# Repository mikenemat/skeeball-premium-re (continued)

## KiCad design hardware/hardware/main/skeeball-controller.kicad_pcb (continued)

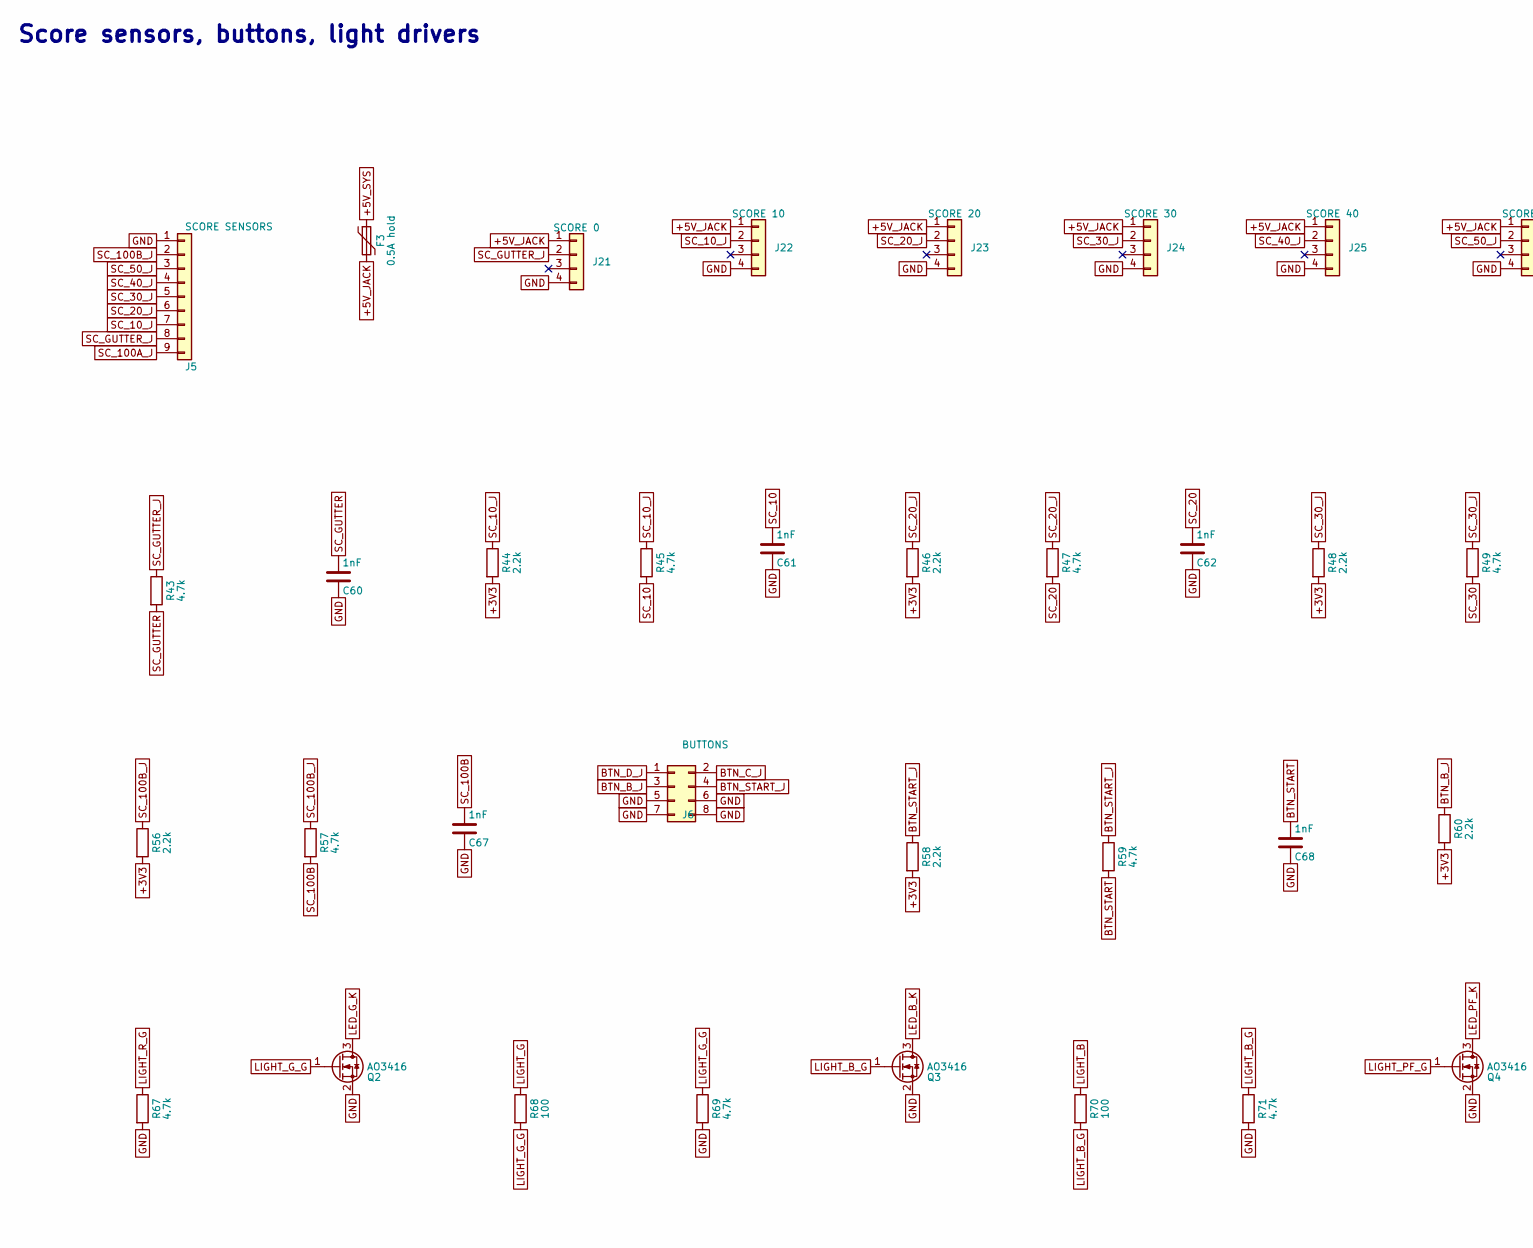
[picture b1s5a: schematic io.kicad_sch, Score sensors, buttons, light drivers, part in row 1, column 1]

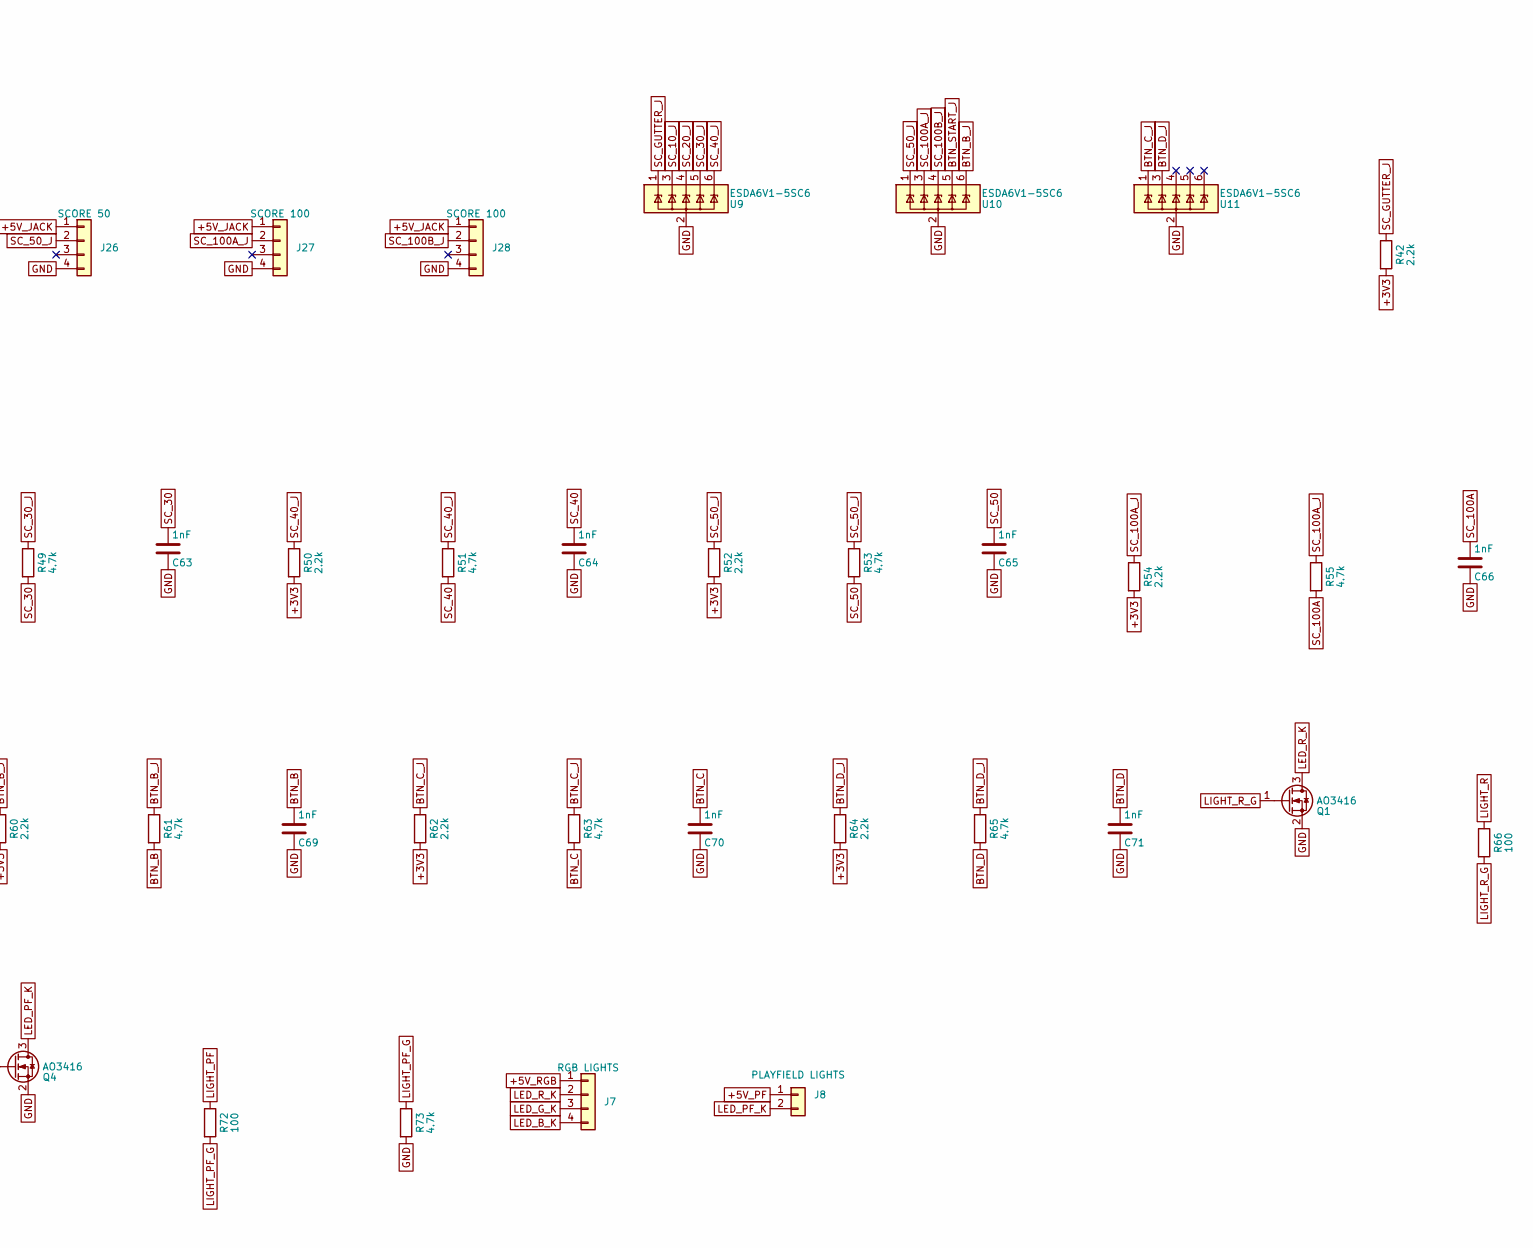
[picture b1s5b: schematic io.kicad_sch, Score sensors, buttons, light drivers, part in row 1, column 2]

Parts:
C60, C61, C62, C63, C64, C65, C66, C67, C68, C69, C70, C71: 1nF; C_0603_1608Metric; MPN CL10B102KB8NNNC
F3: 0.5A hold; Fuse_1206_3216Metric; MPN MF-NSMF050-2; LCSC C75464
J5: SCORE SENSORS; PinHeader_1x09_P2.54mm_Vertical; MPN HC-PZ254-11.5L-1x9PZ; LCSC C27985193
J6: BUTTONS; Molex_Mini-Fit_Jr_5566-08A_2x04_P4.20mm_Vertical; MPN 39281083; LCSC C293503
J7: RGB LIGHTS; Molex_Mini-Fit_Jr_39-30-1049_1x04_P4.20mm_Vertical; MPN 39301049; LCSC C587488
J8: PLAYFIELD LIGHTS; Molex_KK-396_A-41791-0002_1x02_P3.96mm_Vertical; MPN 26604020; LCSC C505042
J21: SCORE 0; RJ11_6P4C_TopEntry_StockPads; MPN 955032441; LCSC C588833
J22: SCORE 10; RJ11_6P4C_TopEntry_StockPads; MPN 955032441; LCSC C588833
J23: SCORE 20; RJ11_6P4C_TopEntry_StockPads; MPN 955032441; LCSC C588833
J24: SCORE 30; RJ11_6P4C_TopEntry_StockPads; MPN 955032441; LCSC C588833
J25: SCORE 40; RJ11_6P4C_TopEntry_StockPads; MPN 955032441; LCSC C588833
J26: SCORE 50; RJ11_6P4C_TopEntry_StockPads; MPN 955032441; LCSC C588833
J27, J28: SCORE 100; RJ11_6P4C_TopEntry_StockPads; MPN 955032441; LCSC C588833
Q1, Q2, Q3, Q4: AO3416; SOT-23; MPN AO3416; LCSC C43307
R42, R44, R46, R48, R50, R52, R54, R56, R58, R60, R62, R64: 2.2k; R_0603_1608Metric; tolerance 1%; MPN 0603WAF2201T5E
R43, R45, R47, R49, R51, R53, R55, R57, R59, R61, R63, R65, R67, R69, R71, R73: 4.7k; R_0603_1608Metric; tolerance 1%; MPN 0603WAF4701T5E
R66, R68, R70, R72: 100; R_0603_1608Metric; tolerance 1%; MPN 0603WAF1000T5E
U9, U10, U11: ESDA6V1-5SC6; SOT-23-6; MPN ESDA6V1-5SC6; LCSC C6650

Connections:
+3V3: R42.2, R44.2, R46.2, R48.2, R50.2, R52.2, R54.2, R56.2, R58.2, R60.2, R62.2, R64.2; also elsewhere on the board
+5V_JACK: F3.2, J21.1, J22.1, J23.1, J24.1, J25.1, J26.1, J27.1, J28.1
+5V_PF: J8.1; also elsewhere on the board
+5V_RGB: J7.1; also elsewhere on the board
+5V_SYS: F3.1; also elsewhere on the board
BTN_B: C69.1, R61.2; also elsewhere on the board
BTN_B_J: J6.3, R60.1, R61.1, U10.6 (IO5)
BTN_C: C70.1, R63.2; also elsewhere on the board
BTN_C_J: J6.2, R62.1, R63.1, U11.1 (IO1)
BTN_D: C71.1, R65.2; also elsewhere on the board
BTN_D_J: J6.1, R64.1, R65.1, U11.3 (IO2)
BTN_START: C68.1, R59.2; also elsewhere on the board
BTN_START_J: J6.4, R58.1, R59.1, U10.5 (IO4)
GND: C60.2, C61.2, C62.2, C63.2, C64.2, C65.2, C66.2, C67.2, C68.2, C69.2, C70.2, C71.2, J5.1, J6.5, J6.6, J6.7, J6.8, J21.4, J22.4, J23.4, J24.4, J25.4, J26.4, J27.4, J28.4, Q1.2 (S), Q2.2 (S), Q3.2 (S), Q4.2 (S), R67.2, R69.2, R71.2, R73.2, U9.2 (GND), U10.2 (GND), U11.2 (GND); also elsewhere on the board
LED_B_K: J7.4, Q3.3 (D)
LED_G_K: J7.3, Q2.3 (D)
LED_PF_K: J8.2, Q4.3 (D)
LED_R_K: J7.2, Q1.3 (D)
LIGHT_B: R70.1; also elsewhere on the board
LIGHT_B_G: Q3.1 (G), R70.2, R71.1
LIGHT_G: R68.1; also elsewhere on the board
LIGHT_G_G: Q2.1 (G), R68.2, R69.1
LIGHT_PF: R72.1; also elsewhere on the board
LIGHT_PF_G: Q4.1 (G), R72.2, R73.1
LIGHT_R: R66.1; also elsewhere on the board
LIGHT_R_G: Q1.1 (G), R66.2, R67.1
SC_10: C61.1, R45.2; also elsewhere on the board
SC_10_J: J5.7, J22.2, R44.1, R45.1, U9.3 (IO2)
SC_20: C62.1, R47.2; also elsewhere on the board
SC_20_J: J5.6, J23.2, R46.1, R47.1, U9.4 (IO3)
SC_30: C63.1, R49.2; also elsewhere on the board
SC_30_J: J5.5, J24.2, R48.1, R49.1, U9.5 (IO4)
SC_40: C64.1, R51.2; also elsewhere on the board
SC_40_J: J5.4, J25.2, R50.1, R51.1, U9.6 (IO5)
SC_50: C65.1, R53.2; also elsewhere on the board
SC_50_J: J5.3, J26.2, R52.1, R53.1, U10.1 (IO1)
SC_100A: C66.1, R55.2; also elsewhere on the board
SC_100A_J: J5.9, J27.2, R54.1, R55.1, U10.3 (IO2)
SC_100B: C67.1, R57.2; also elsewhere on the board
SC_100B_J: J5.2, J28.2, R56.1, R57.1, U10.4 (IO3)
SC_GUTTER: C60.1, R43.2; also elsewhere on the board
SC_GUTTER_J: J5.8, J21.2, R42.1, R43.1, U9.1 (IO1)

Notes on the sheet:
Score sensors, buttons, light drivers

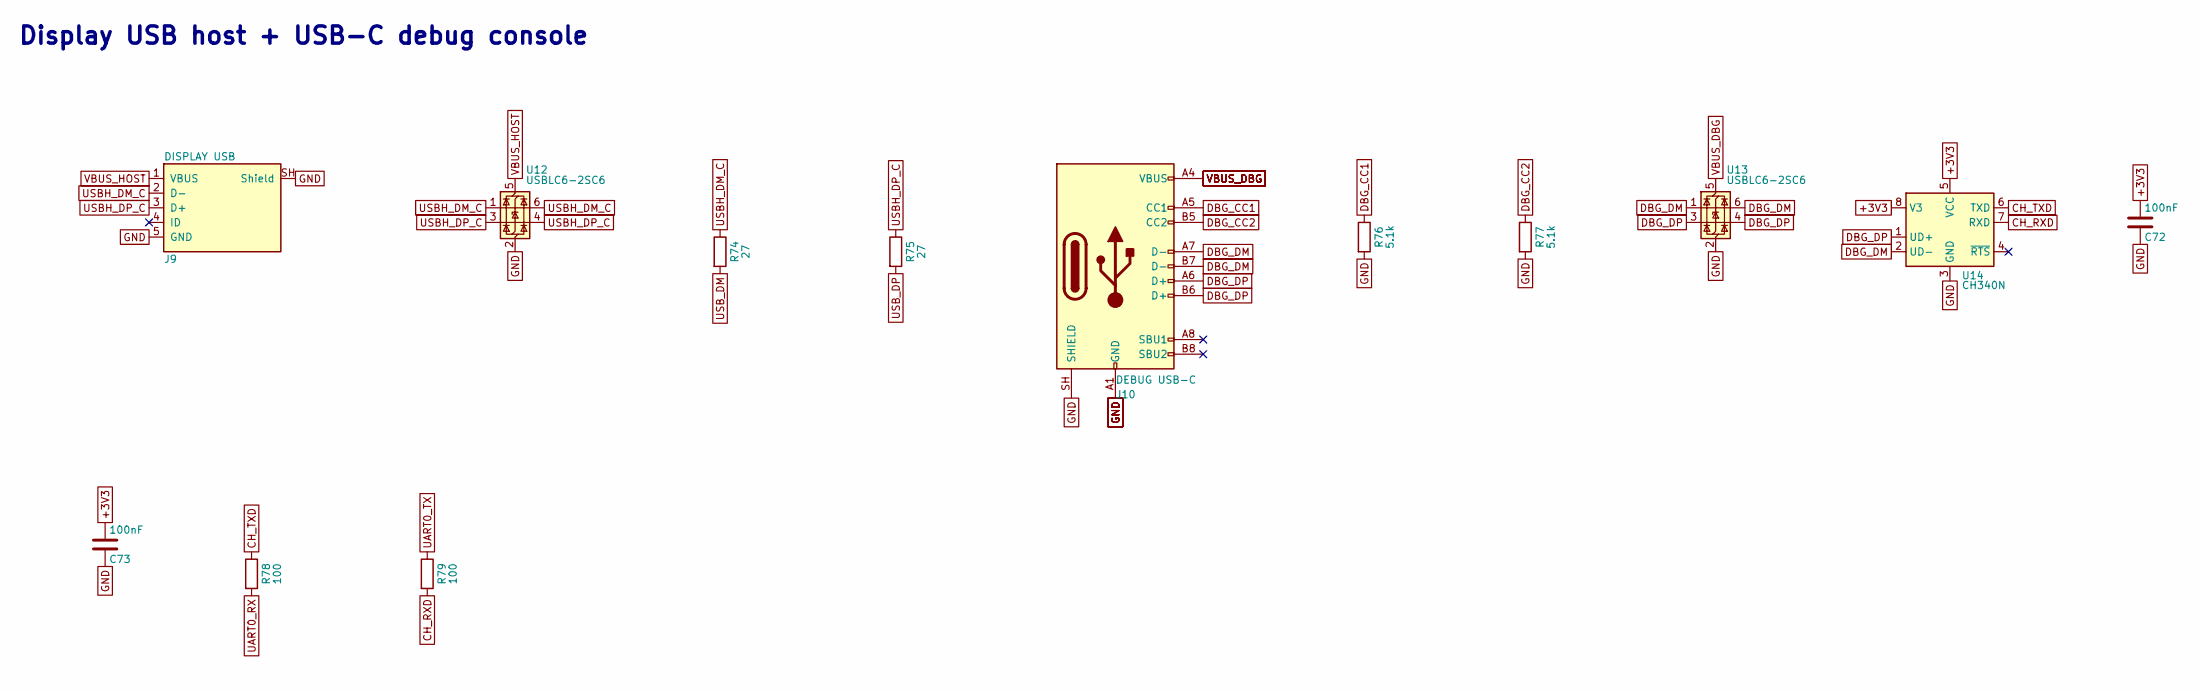
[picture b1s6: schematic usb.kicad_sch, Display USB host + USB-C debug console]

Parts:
C72, C73: 100nF; C_0603_1608Metric; MPN CC0603KRX7R9BB104
J9: DISPLAY USB; USB_Micro-B_Amphenol_10118194-0001LF_Horizontal; MPN 10118194-0001LF; LCSC C132563
J10: DEBUG USB-C; USB_C_Receptacle_HRO_TYPE-C-31-D-15_Vertical; MPN TYPE-C-31-D-15; LCSC C22464480
R74, R75: 27; R_0603_1608Metric; tolerance 1%; MPN 0603WAF270JT5E
R76, R77: 5.1k; R_0603_1608Metric; tolerance 1%; MPN 0603WAF5101T5E
R78, R79: 100; R_0603_1608Metric; tolerance 1%; MPN 0603WAF1000T5E
U12, U13: USBLC6-2SC6; SOT-23-6; MPN USBLC6-2SC6; LCSC C7519
U14: CH340N; SOIC-8_3.9x4.9mm_P1.27mm; MPN CH340N; LCSC C2977777

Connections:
+3V3: C72.1, C73.1, U14.5 (VCC), U14.8 (V3); also elsewhere on the board
CH_RXD: R79.2, U14.7 (RXD)
CH_TXD: R78.1, U14.6 (TXD)
DBG_CC1: J10.A5 (CC1), R76.1
DBG_CC2: J10.B5 (CC2), R77.1
DBG_DM: J10.A7 (D-), J10.B7 (D-), U13.1 (I/O1), U13.6 (I/O1), U14.2 (UD-)
DBG_DP: J10.A6 (D+), J10.B6 (D+), U13.3 (I/O2), U13.4 (I/O2), U14.1 (UD+)
GND: C72.2, C73.2, J9.5 (GND), J9.SH (Shield), J10.A1 (GND), J10.A12 (GND), J10.B1 (GND), J10.B12 (GND), J10.SH (SHIELD), R76.2, R77.2, U12.2 (GND), U13.2 (GND), U14.3 (GND); also elsewhere on the board
UART0_RX: R78.2; also elsewhere on the board
UART0_TX: R79.1; also elsewhere on the board
USBH_DM_C: J9.2 (D-), R74.1, U12.1 (I/O1), U12.6 (I/O1)
USBH_DP_C: J9.3 (D+), R75.1, U12.3 (I/O2), U12.4 (I/O2)
USB_DM: R74.2; also elsewhere on the board
USB_DP: R75.2; also elsewhere on the board
VBUS_DBG: J10.A4 (VBUS), J10.A9 (VBUS), J10.B4 (VBUS), J10.B9 (VBUS), U13.5 (VBUS)
VBUS_HOST: J9.1 (VBUS), U12.5 (VBUS); also elsewhere on the board

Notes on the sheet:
Display USB host + USB-C debug console

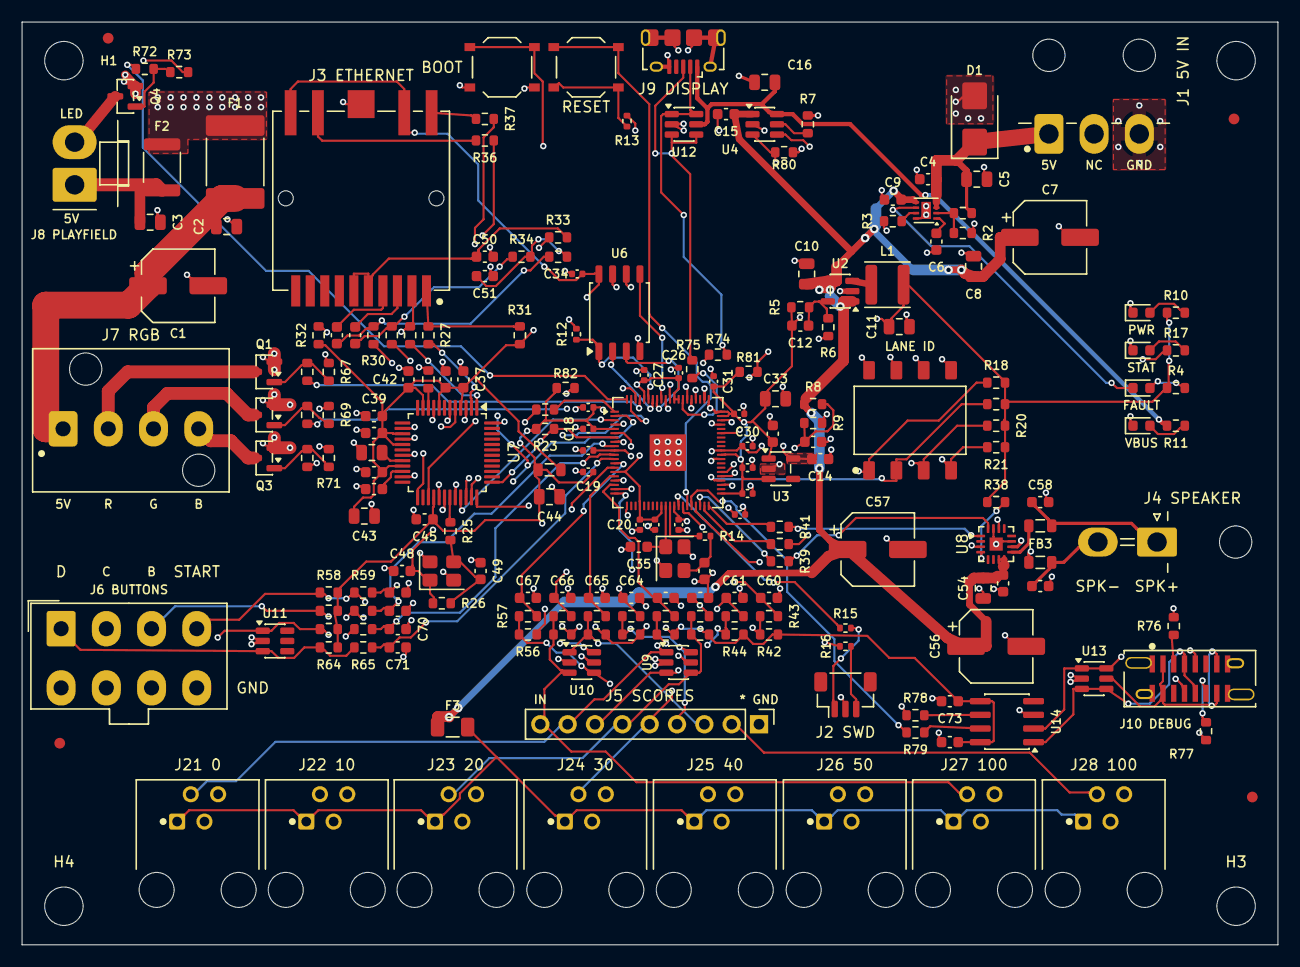
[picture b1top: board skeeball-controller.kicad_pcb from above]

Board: 4 copper layers, 116.7 x 85.7 mm, 216 parts (0 on the bottom side), 133 nets.

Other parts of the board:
FID1, FID2, FID3, FID4: Fiducial; Fiducial_1mm_Mask2mm

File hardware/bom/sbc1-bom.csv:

Refs,Qty/board,Value,MPN,Maker,LCSC,JLC library,JLC stock,Unit USD (JLC),Checked (UTC),Status,Notes
"C47, C51",2,10nF,0603B103K500NT,FH,C57112,basic,5972499,0.0047,2026-10-27,OK,
"C52, C53",2,6.8nF,0603B682K500NT,FH,C1631,basic,364930,0.0055,2026-10-27,OK,
"C4, C9, C15, C17, C37, C38, C39, C40, C41, C42, C45, C55, C72, C73",14,100nF,CC0603KRX7R9BB104,YAGEO,C14663,basic,42860043,0.0149,2026-10-27,OK,
"C31, C32",2,4.7uF,CL05A475MP5NRNC,Samsung,C23733,basic,2606160,0.0153,2026-10-27,OK,
"C18, C19, C20, C21, C22, C23, C24, C25, C26, C27, C28, C29, C30, C34",14,100nF,CL05B104KO5NNNC,Samsung,C1525,basic,34906725,0.0035,2026-10-27,OK,
"C13, C14",2,1uF,CL10A105KB8NNNC,Samsung,C15849,basic,13334380,0.0146,2026-10-27,OK,
"C58, C59, C60, C61, C62, C63, C64, C65, C66, C67, C68, C69, C70, C71",14,1nF,CL10B102KB8NNNC,Samsung,C1588,basic,5502112,0.0098,2026-10-27,OK,
C50,1,22nF,CL10B223KB8NNNC,Samsung,C21122,basic,1077610,0.0057,2026-10-27,OK,
C6,1,47nF,CL10B473KB8NNNC,Samsung,C1622,basic,974968,0.0077,2026-10-27,OK,
"C12, C35, C36",3,15pF C0G,CL10C150JB8NNNC,Samsung,C1644,basic,1119169,0.0111,2026-10-27,OK,
"C48, C49",2,18pF C0G,CL10C180JB8NNNC,Samsung,C1647,basic,271473,0.0158,2026-10-27,OK,
"C2, C3, C5, C11, C33, C43, C44, C54",8,10uF,CL21A106KAYNNNE,Samsung,C15850,basic,8948721,0.0438,2026-10-27,OK,
"C8, C16",2,22uF,CL21A226MAQNNNE,Samsung,C45783,basic,4118242,0.1917,2026-10-27,OK,
"C10, C46",2,4.7uF,CL21A475KAQNNNE,Samsung,C1779,basic,1980619,0.0343,2026-10-27,OK,
"C1, C7, C56, C57",4,220uF polymer,OVZ221M1ATR-0606,Lelon,C311623,extended,15012,0.2063,2026-10-27,OK,
"D3, D5",2,PWR green,KT-0603G,Hubei KENTO,C12624,extended,443493,0.0117,2026-10-27,OK,
D2,1,FAULT red,KT-0603R,Hubei KENTO,C2286,basic,7642560,0.0077,2026-10-27,OK,
D4,1,VBUS yellow,NCD0603Y1,NationStar,C84268,extended,306447,0.0112,2026-10-27,OK,
D1,1,SMBJ5.0A,SMBJ5.0A,Littelfuse,C83333,extended,37387,0.1156,2026-10-27,OK,
F2,1,3A hold,1812L300MR,Littelfuse,C127824,extended,3798,0.1366,2026-10-27,OK,
F1,1,5A hold,2920L500/16MR,Littelfuse,C207091,extended,2614,0.3788,2026-10-27,OK,
"FB2, FB3",2,BLM21PG221SN1D,BLM21PG221SN1D,Murata,C85840,extended,591700,0.0346,2026-10-27,OK,
FB1,1,600R@100MHz,GZ2012D601TF,Sunlord,C1017,basic,577061,0.02,2026-10-27,OK,
F3,1,0.5A hold,MF-NSMF050-2,Bourns,C75464,extended,72093,0.0591,2026-10-27,OK,
J9,1,DISPLAY USB,10118194-0001LF,Amphenol ICC,C132563,extended,41020,0.2585,2026-10-27,OK,harness
J8,1,PLAYFIELD LIGHTS,26604020,Molex,C505042,extended,24726,0.1605,2026-10-27,OK,harness
J6,1,BUTTONS,39281083,Molex,C293503,extended,4243,0.402,2026-10-27,OK,harness
J4,1,SPEAKER,39300020,Molex,C240831,extended,298,0.604,2026-10-27,OK,harness
J7,1,RGB LIGHTS,39301049,Molex,C587488,extended,4042,0.3192,2026-10-27,OK,harness
J1,1,PWR 5V/GND,39303035,Molex,C505179,extended,11634,0.5369,2026-10-27,OK,harness
"J21, J22, J23, J24, J25, J26, J27, J28",8,SCORE 0,955032441,Molex,C588833,extended,649,1.1114,2026-10-27,OK,harness
J2,1,SWD,BM03B-SRSS-TB(LF)(SN),JST,C160389,extended,27324,0.2762,2026-10-27,OK,
J5,1,SCORE SENSORS,HC-PZ254-11.5L-1x9PZ,Hong Cheng,C27985193,extended,2390,0.0433,2026-10-27,OK,harness
J3,1,HR963380AE,HR963380AE,HanRun,C19724763,extended,154,2.7252,2026-10-27,OK,
J10,1,DEBUG USB-C,TYPE-C-31-D-15,Korean Hroparts,C22464480,extended,469,0.6531,2026-10-27,OK,
L1,1,2.2uH,SWPA4030S2R2MT,Sunlord,C36409,extended,34358,0.0583,2026-10-27,OK,
"Q1, Q2, Q3, Q4",4,AO3416,AO3416,Alpha & Omega,C43307,extended,48177,0.1091,2026-10-27,OK,
"R15, R16",2,100,0402WGF1000TCE,UNI-ROYAL,C25076,basic,7105177,0.0012,2026-10-27,OK,
"R12, R13, R14",3,1k,0402WGF1001TCE,UNI-ROYAL,C11702,basic,19064680,0.0013,2026-10-27,OK,
"R25, R27, R28, R29, R30",5,0,0603WAF0000T5E,UNI-ROYAL,C21189,basic,22071302,0.0022,2026-10-27,OK,
"R66, R68, R70, R72, R78, R79",6,100,0603WAF1000T5E,UNI-ROYAL,C22775,basic,10427539,0.0023,2026-10-27,OK,
"R4, R10",2,1k,0603WAF1001T5E,UNI-ROYAL,C21190,basic,34230068,0.0017,2026-10-27,OK,
"R18, R19, R20, R21, R23, R81, R82",7,10k,0603WAF1002T5E,UNI-ROYAL,C25804,basic,38841065,0.0017,2026-10-27,OK,
"R1, R5, R8",3,100k,0603WAF1003T5E,UNI-ROYAL,C25803,basic,17660400,0.0031,2026-10-27,OK,
R26,1,1M,0603WAF1004T5E,UNI-ROYAL,C22935,basic,5584345,0.0018,2026-10-27,OK,
R33,1,10,0603WAF100JT5E,UNI-ROYAL,C22859,basic,6801213,0.0032,2026-10-27,OK,
R22,1,12.4k,0603WAF1242T5E,UNI-ROYAL,C22865,extended,183987,0.0015,2026-10-27,OK,
R11,1,1.5k,0603WAF1501T5E,UNI-ROYAL,C22843,basic,3838230,0.002,2026-10-27,OK,
"R42, R44, R46, R48, R50, R52, R54, R56, R58, R60, R62, R64",12,2.2k,0603WAF2201T5E,UNI-ROYAL,C4190,basic,5955416,0.0018,2026-10-27,OK,
R6,1,22k,0603WAF2202T5E,UNI-ROYAL,C31850,basic,3147116,0.0042,2026-10-27,OK,
"R74, R75",2,27,0603WAF270JT5E,UNI-ROYAL,C25190,preferred,407953,0.0016,2026-10-27,OK,
"R36, R37",2,330,0603WAF3300T5E,UNI-ROYAL,C23138,basic,3725238,0.002,2026-10-27,OK,
"R24, R39, R40, R41",4,33,0603WAF330JT5E,UNI-ROYAL,C23140,basic,4510286,0.0024,2026-10-27,OK,
R17,1,470,0603WAF4700T5E,UNI-ROYAL,C23179,basic,4990526,0.0023,2026-10-27,OK,
"R43, R45, R47, R49, R51, R53, R55, R57, R59, R61, R63, R65, R67, R69, R71, R73, R80",17,4.7k,0603WAF4701T5E,UNI-ROYAL,C23162,basic,16608030,0.0028,2026-10-27,OK,
"R2, R9",2,47k,0603WAF4702T5E,UNI-ROYAL,C25819,basic,3388230,0.0035,2026-10-27,OK,
R7,1,49.9k,0603WAF4992T5E,UNI-ROYAL,C23184,basic,1592716,0.0029,2026-10-27,OK,
"R31, R32, R34, R35",4,49.9,0603WAF499JT5E,UNI-ROYAL,C23185,basic,1633061,0.0021,2026-10-27,OK,
"R76, R77",2,5.1k,0603WAF5101T5E,UNI-ROYAL,C23186,basic,21976225,0.0015,2026-10-27,OK,
R38,1,510k,0603WAF5103T5E,UNI-ROYAL,C23192,basic,950956,0.002,2026-10-27,OK,
R3,1,680,0603WAF6800T5E,UNI-ROYAL,C23228,basic,1992590,0.0021,2026-10-27,OK,
SW3,1,LANE ID,DSIC04LS-P,XKB Connection,C319038,extended,6316,0.6367,2026-10-27,OK,
"SW1, SW2",2,BOOTSEL,TS-1187A-B-A-B,XKB Connection,C318884,basic,1187372,0.0207,2026-10-27,OK,
U14,1,CH340N,CH340N,WCH,C2977777,extended,24904,0.5909,2026-10-27,OK,
"U9, U10, U11",3,ESDA6V1-5SC6,ESDA6V1-5SC6,STMicroelectronics,C6650,extended,2981,0.2115,2026-10-27,OK,
U8,1,MAX98357AETE+T,MAX98357AETE+T,Analog Devices,C910544,extended,33473,1.3242,2026-10-27,OK,
U5,1,RP2350B,RP2350B,Raspberry Pi,C42415655,extended,3477,1.2833,2026-10-27,OK,
U2,1,TLV62569DBVR,TLV62569DBVR,Texas Instruments,C141836,extended,432314,0.0708,2026-10-27,OK,
U3,1,TLV74311PDBVR,TLV74311PDBVR,Texas Instruments,C485147,extended,10298,0.0935,2026-10-27,OK,
U4,1,TPS2553DBVR,TPS2553DBVR,Texas Instruments,C55266,extended,49261,0.5418,2026-10-27,OK,
U1,1,TPS259531DSGR,TPS259531DSGR,Texas Instruments,C2155674,extended,2161,0.8773,2026-10-27,OK,
"U12, U13",2,USBLC6-2SC6,USBLC6-2SC6,STMicroelectronics,C7519,extended,37197,0.1797,2026-10-27,OK,
U6,1,W25Q128JVSIQ,W25Q128JVSIQ,Winbond,C97521,basic,58346,2.5828,2026-10-27,OK,
U7,1,W5500,W5500,WIZnet,C32843,extended,23251,2.83,2026-10-27,OK,
Y1,1,12MHz,ABM8-272-T3,Abracon,C20625731,extended,2735,0.658,2026-10-27,OK,
Y2,1,25MHz,X322525MOB4SI,YXC,C9006,basic,240479,0.0951,2026-10-27,OK,

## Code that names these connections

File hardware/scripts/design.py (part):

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# GPIO map = escape order of the RP2350B pins (owner 2026-10-26: the firmware is an original implementation, the stock
# RP2040 roles are lifted; DECISIONS #8). The 8 score lines leave the LEFT side top -> bottom in the RC grid's
# left -> right column order (100B .. gutter), so the bundle fans out to the grid without a crossing.
SCORE_GPIO = {"SC_100B": 14, "SC_100A": 15, "SC_50": 16, "SC_40": 17, "SC_30": 18, "SC_20": 19, "SC_10": 20,
              "SC_GUTTER": 21}
J11_PINMAP = {1: GND, 2: "SC_100B", 3: "SC_50", 4: "SC_40", 5: "SC_30", 6: "SC_20", 7: "SC_10", 8: "SC_GUTTER",
              9: "SC_100A"}
# ^ pin 1 = the '*' square pad (right end, top view) = the switches' common = GND (owner continuity 2026-10-26).
#   Score order = owner continuity 2026-10-27, NOT linear: top view, jacks 1-8 left -> right (J21-J28, labels
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#   a bottom-side trace runs from the leftmost header pin along the row to the first '100' jack's contact-2 tail.
#   J11 carries NO 5 V
BUTTONS = ["BTN_START", "BTN_B", "BTN_C", "BTN_D"]
BUTTON_GPIO = {"BTN_START": 10, "BTN_B": 11, "BTN_C": 12, "BTN_D": 13}   # B/C/D = VOLUME/GAME/PLAYERS, order CONFIRM;
# left side above the score lines (outermost of the south-west bundle toward the buttons RC block / U11)
BUTTONS_PINMAP = {1: "BTN_D", 2: "BTN_C", 3: "BTN_B", 4: "BTN_START", 5: GND, 6: GND, 7: GND, 8: GND}
# ^ owner continuity 2026-10-26: the whole bottom row (the latch side, component face up) = GND, the top row = the four
#   button signals (START / GAME / PLAYERS / VOLUME order = firmware), left to right on the board D C B START.
#   Molex 39-28-1083 / KiCad 5566-08A: the latch is on the circuits 5-8 row (KiCad fab + JLC C293503 footprint and 3D
#   model agree; verified 2026-10-27 after the owner saw the latch 180 deg off in the render) -> 5-8 = GND (latch row,
#   scan y 61.7), 1-4 = the signals (scan y 56.2), footprint at 0 deg with pin 1 = the leftmost signal pin
POWER_PINMAP = {1: V5IN, 2: "NC_PWR_MID", 3: GND}  # owner 2026-10-26: middle pin not connected; 1 = 5 V, 3 = GND
RGB_PINMAP = {1: V5RGB, 2: "LED_R_K", 3: "LED_G_K", 4: "LED_B_K"}   # pin 1 (leftmost, square pad, black wire)
# = +5 V by owner continuity 2026-10-26 (common anode confirmed); the R / G / B order of pins 2-4 is a firmware matter
PLAYFIELD_PINMAP = {1: V5PF, 2: "LED_PF_K"}   # pin 1 = the LOWER pin (nearer the RGB connector, farther from
# the top edge, component side up) = +5 V by owner continuity 2026-10-26; the upper pin = low-side FET channel
SPEAKER_PINMAP = {1: "SPK_P", 2: "SPK_N"}                         # bridge-tied load: neither side is ground

# RJ45 (owner decision 2026-10-26): zone a (stock model-number silk area), VERTICAL jack = "V" (HanRun HR963380AE);
# "RA" (HanRun HR911105A right-angle) is kept in the generator only as the fallback if the vertical part runs out.
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D.add("D", "Device:LED", "FAULT red", "LED_SMD:LED_0603_1608Metric", S, {"A": "LED_FAULT_A", "K": "PWR_FAULT_N"},
      mpn="KT-0603R", mfr="Hubei KENTO", LCSC="C2286",
      note="FAULT LED on the wired-OR open-drain fault line (eFuse FLT + TPS2553 FAULT): lit = over-current / "
           "over-temperature / OV clamp on a rail; the line is also read on GPIO47. Hubei KENTO KT-0603R, JLC basic "
           "(Economic-PCBA eligible; NationStar NCD0603R1 C84263 is Standard-PCBA-only per JLC's assembly review "
           "2026-10-27). KENTO drawing: pad 1 = '+' (anode); C2286's LCSC symbol / footprint agree (pin 1 = A, "
           "layer-101 polarity dot on pad 1), so JLC's preview dot marks the ANODE on this part; fab_release.py maps "
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res("1k", V3, "LED_FAULT_A", S, note="FAULT LED current ~1.3 mA (LED in series: this is NOT the line's pull-up, R81 is)")
D.add("R81", "Device:R", "10k", "Resistor_SMD:R_0603_1608Metric", S, {"1": V3, "2": "PWR_FAULT_N"},
      mpn=r_mpn("10k"), mfr="UNI-ROYAL", tolerance="1%", fixed_ref=True,
      note="PWR_FAULT_N pull-up (TPS2595 SLVSE57C pin table: FLT open drain, 'requires an external pull up "
           "resistance'; logic review L-01 2026-10-27): the line idles at 3.3 V (RP2350 VIH 2.0 V); the FAULT LED "
           "still lights at ~1.3 mA when a FLT / FAULT pin pulls low. Fixed ref after R80 (routed board refs stay)")
cap("220uF polymer", V5, GND, S, note="+5V_SYS bulk at the eFuse output; polymer (owner 2026-10-26)")
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    D.add("U", "skeeball:TPS2553DBV", "TPS2553DBVR", "Package_TO_SOT_SMD:SOT-23-6", S,
          {"IN": V5, "EN": "VBUS_HOST_EN", "GND": GND, "OUT": out, "~{FAULT}": "PWR_FAULT_N", "ILIM": f"ILIM_{name}"},
          mpn="TPS2553DBVR", mfr="Texas Instruments", LCSC="C55266",
          note=f"{note}; limit 0.43-0.52 A (RILIM 49.9k, SLVS841F 7.5); EN = GPIO46 (VBUS_HOST_EN, active high) with a "
               "100k pull-down: VBUS_HOST stays off through reset / BOOTSEL until firmware enables it (adversarial "
               "review F08 2026-10-27: EN on +3V3 sourced VBUS into a PC on the BOOTSEL recovery cable)")
    cap("100nF", V5, GND, S, note="IN bypass 0.1 uF (10.2)")
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    cap("22uF", out, GND, S, note="output cap (TI recommends a large output cap for transient loads)")
D.add("R80", "Device:R", "4.7k", "Resistor_SMD:R_0603_1608Metric", S, {"1": "VBUS_HOST_EN", "2": GND},
      mpn=r_mpn("4.7k"), mfr="UNI-ROYAL", tolerance="1%", fixed_ref=True,
      note="U4 EN pull-down: TPS2553 off while GPIO46 is high-Z (RP2350 reset state: output Hi-Z, pulled low, DS 9.3). "
           "4.7k (<= 8.2k) so a GPIO turned from driven-high to input with IE set cannot hold the pad at ~2.2 V "
           "(RP2350-E9, DS D.5.1; logic review L-10 2026-10-27; was 100k); 0.7 mA while EN is driven high. "
           "Fixed ref R80 = after the last auto-numbered resistor (R79), so the routed board's refs do not shift")

D.block = "pwr_mon"
res("100k", V5, "VSYS_SENSE", S, note="+5V_SYS monitor: 5.9 V -> 1.89 V at ADC0 (GPIO40); firmware logs the rail")
res("47k", "VSYS_SENSE", GND, S)
cap("100nF", "VSYS_SENSE", GND, S)
D.block = "pwr_led"
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

for k, net in enumerate(("LIGHT_R", "LIGHT_G", "LIGHT_B", "LIGHT_PF")):
    g(k, net)                                         # stock GPIO0-3 = the four light outputs (colour order CONFIRM)
for b, n in BUTTON_GPIO.items():
    g(n, b)
for s_, n in SCORE_GPIO.items():
    g(n, s_)
# pin-escape map (DECISIONS #8, RP2350 datasheet Table 3 bank-0 functions checked per pin):
#   left side, top: W5500 on SPI0 = GPIO4 RX (MISO) / 5 CSn / 6 SCK / 7 TX (MOSI) (F1), INTn GPIO8, RSTn GPIO9 -> west
#   to U7 above the score / button bundle;
#   bottom right: UART0 TX GPIO28 / RX GPIO29 (F2) -> east to the CH340N; I2S (PIO, GPIOBASE 16 window) BCLK GPIO30,
#   LRCLK GPIO31 (= BCLK + 1, the pico-extras audio_i2s order), DIN GPIO32 -> east to R39-R41 / U8;
#   right side: lane-ID DIP GPIO34-37 -> east to SW3; status LED GPIO44 and the fault flag GPIO47 -> up-right.
g(47, "PWR_FAULT_N")                                   # eFuse / switch fault flag (wired-OR, open drain)
g(9, "ETH_RST_N")                                      # W5500 RSTn, MCU-driven (WIZnet reference)
g(8, "ETH_INT_N")                                      # W5500 INTn
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g(7, "ETH_MOSI")
g(44, "LED_STATUS")
g(46, "VBUS_HOST_EN")                                  # U4 TPS2553 EN (+ R80 100k pull-down), adversarial review F08;
                                                       # Table 3 GPIO46: SIO / PWM11 A / SPI1 SCK / PIO (pin 57, next to
                                                       # the PWR_FAULT_N pin 58 lane to U4)
g(30, "I2S_BCLK_MCU")
g(31, "I2S_LRCLK_MCU")
g(32, "I2S_DIN_MCU")
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
D.block = "status"
D.add("D", "Device:LED", "STATUS green", "LED_SMD:LED_0603_1608Metric", S, {"A": "LED_STATUS_A", "K": GND},
      mpn="KT-0603G", mfr="Hubei KENTO", LCSC="C12624", note="heartbeat on GPIO44 (pin-escape map, DECISIONS #8; the stock board used GPIO27)")
res("470", "LED_STATUS", "LED_STATUS_A", S)

D.block = "laneid"
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# channel; current_budget LED_*_K, adversarial review F05 2026-10-27: the earlier "~3 A per channel" and "drain copper
# pour" claims are withdrawn - the drains run on 1.0-1.2 mm F.Cu tracks): ~32 mOhm hot x 4 A^2 = 0.13 W per FET.
# AO3400A (48 mOhm at 2.5 V) would be ~0.2 W at 2 A and 0.6 W at 3 A.
# PWM dimming / colour mixing of the EXISTING strips (owner 2026-10-26): GPIO0-3 = PWM slices 0A/0B/1A/1B; Qg ~10 nC
# through 100 R from a 12 mA pad switches in ~1 us, < 0.5 % of a 5 kHz period - negligible switching loss.
for ch, kn in (("LIGHT_R", "LED_R_K"), ("LIGHT_G", "LED_G_K"), ("LIGHT_B", "LED_B_K"), ("LIGHT_PF", "LED_PF_K")):
    D.add("Q", "Transistor_FET:Q_NMOS_GSD", "AO3416", "Package_TO_SOT_SMD:SOT-23", S,
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
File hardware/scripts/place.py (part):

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put("C12", 72.3, 28.2, 0)         # feed-forward across R5
# VBUS switch for the display port, next to J9
put("R80", 70.8, 12.1, 0)         # U4 EN 4.7k pull-down (q5, adversarial review F08; q6 4.7k RP2350-E9), pad 1 toward EN pin 3
# q6 (2026-10-27, coordinator QA B1 / B2): PWR_FAULT_N pull-up R81 beside the U5 pin-58 escape, ETH_CS_N pull-up R82
# above-left of U5 (free courtyard spots found by .runtime/route/q6/tools/spot.py on the routed q5 board)
put("R81", 67.5, 32.5, 0)
put("R82", 50.5, 34.0, 0)
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put("U6", 55.5, 27.0, 90)         # W25Q128 above-left (QSPI pins 70-75 on the MCU's top side)
put("C34", 51.58, 23.4, 180)
put("R12", 51.5, 29.0, 90)        # BOOTSEL 1k on QSPI_SS, at the flash (button stub isolated by 1k)
put("Y1", 60.65, 49.85, 270)      # 12 MHz: XIN pad 1 straight under pin 30 (q5 placement wave, 2026-10-27)
put("C35", 57.3, 48.75, 180)     # XIN load: pad 1 beside Y1 pad 1
put("C36", 63.4, 51.0, 270)      # XOUT_X load beside Y1 pad 3
# q6 (coordinator QA B5, logic review L-02): R14 horizontal in the lane between C29 / Y1 pad 4, right of the Y1 courtyard;
# XOUT = locked F.Cu stub, no via (power_copper.Q6_XTAL): down the 0.6 mm lane between XIN and C29, under C29, to R14.1;
# XOUT_X straight down to C36.1 / Y1.3. R14 cannot sit against pin 31: XIN (pin 30) and C29 (DVDD pin 32) flank it
put("R14", 63.45, 47.755, 0)     # 1k XOUT series (courtyard clear of the Y1 courtyard at x 62.445)
# +5V_SYS monitor divider (ADC0 = pin 49, right side)
row(["R8", "R9", "C17"], 73.5, 35.5, 0, 1.75)
# I2S series resistors at the MCU (source end)
row(["R41", "R40", "R39"], 70.4, 46.9, 0, 1.6)     # pass 5: +0.8 x = a lane; DIN / LRCLK / BCLK top -> bottom = the
                                                    # eastward order of U5 pins 40 / 39 / 38 (GPIO32 / 31 / 30, DECISIONS #8)

# ---- Ethernet: W5500 below the jack (MDI pins up), terminations between them --------------------------------------
put("U7", 39.5, 40.0, 270)
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# pins 1 / 2, qa_placement DIFFPAIR-PLACE), straight under their pins
row(["R27", "R28", "R29", "R30", "C52", "C53"], 37.75, 29.1, -1.7, 0, 90)
# top side (pass 5): 0.5 mm closer to the pins (courtyards 0.07 clear of U7) and R22 straight over EXRES (pin 10): in
# p8 / p9 the pin-9 GND drop via took the 0.6 mm lane between pin 10 and R22.1 and ETH_EXRES stayed open; now the
# R22.1 - pin 10 gap (0.6 mm) holds the EXRES stub only
put("C37", 41.0, 33.2, 90)        # pin 4
put("C41", 39.35, 33.2, 90)       # pin 8
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put("C47", 32.7, 43.39, 180)      # 1V2 10 nF
put("C43", 31.8, 45.9, 0)         # 3V3A 10 uF
# crystal group (pass 5): R25 (0R, XO -> XO_X) straight between U7 pin 31 and Y2 pin 3, Y2 / C48 / C49 2 mm lower, the
# 1M R26 under Y2 - the U7 bottom-right corner (SPI pins 32-36 toward U5) is left clear (p8: ETH_MOSI / ETH_INT_N open)
put("C45", 37.4, 46.2, 180)       # pin 28 (digital 3V3): pad 1 under the pin
put("R25", 39.8, 47.3, 270)
put("Y2", 39.0, 51.0, 0)
put("C48", 35.3, 51.0, 180)        # XI cap: pad 1 toward Y2 pin 1, clear of C68
put("C49", 42.6, 51.0, 90)
put("R26", 39.0, 54.0, 0)
# W5500 SPI / RSTn now on U5's top-left pins (GPIO4-9, DECISIONS #8): MISO 33R + RSTn pull-up beside them, the 3V3A
# filter below
put("R24", 48.6, 36.0, 0)         # MISO 33R
put("R23", 48.6, 37.8, 0)         # RSTn pull-up
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# ---- score inputs: ESD at J11, RC grid between the MCU and J11 ---------------------------------------------------------
put("U9", 61.0, 59.5, 0)
put("U10", 52.0, 59.5, 0)
SC = ["SC_100B", "SC_100A", "SC_50", "SC_40", "SC_30", "SC_20", "SC_10", "SC_GUTTER"]   # left -> right (J11 pins 9 -> 2)
by_net = {}
for p in D.parts.values():
    if p.block == "scores" and p.ref.startswith(("R", "C")):
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
def main():
    board = pcbnew.LoadBoard(str(BOARD))
    for d in list(board.GetDrawings()):                    # idempotent: drop pin labels of a previous run
        if isinstance(d, pcbnew.PCB_TEXT) and d.GetLayer() == pcbnew.F_SilkS:
            board.Remove(d)
    for fp in list(board.GetFootprints()):                 # idempotent: keep only the holes from pcb_build.py
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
